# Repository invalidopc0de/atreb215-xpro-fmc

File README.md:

# ATREB215-XPRO FMC Adapter

This repo contains the schematics and PCB layout for a board to adapt
the SATA connectors on the ATREB215 breakout board to the FMC connector 
on a Lattice CrossLink-NX development board

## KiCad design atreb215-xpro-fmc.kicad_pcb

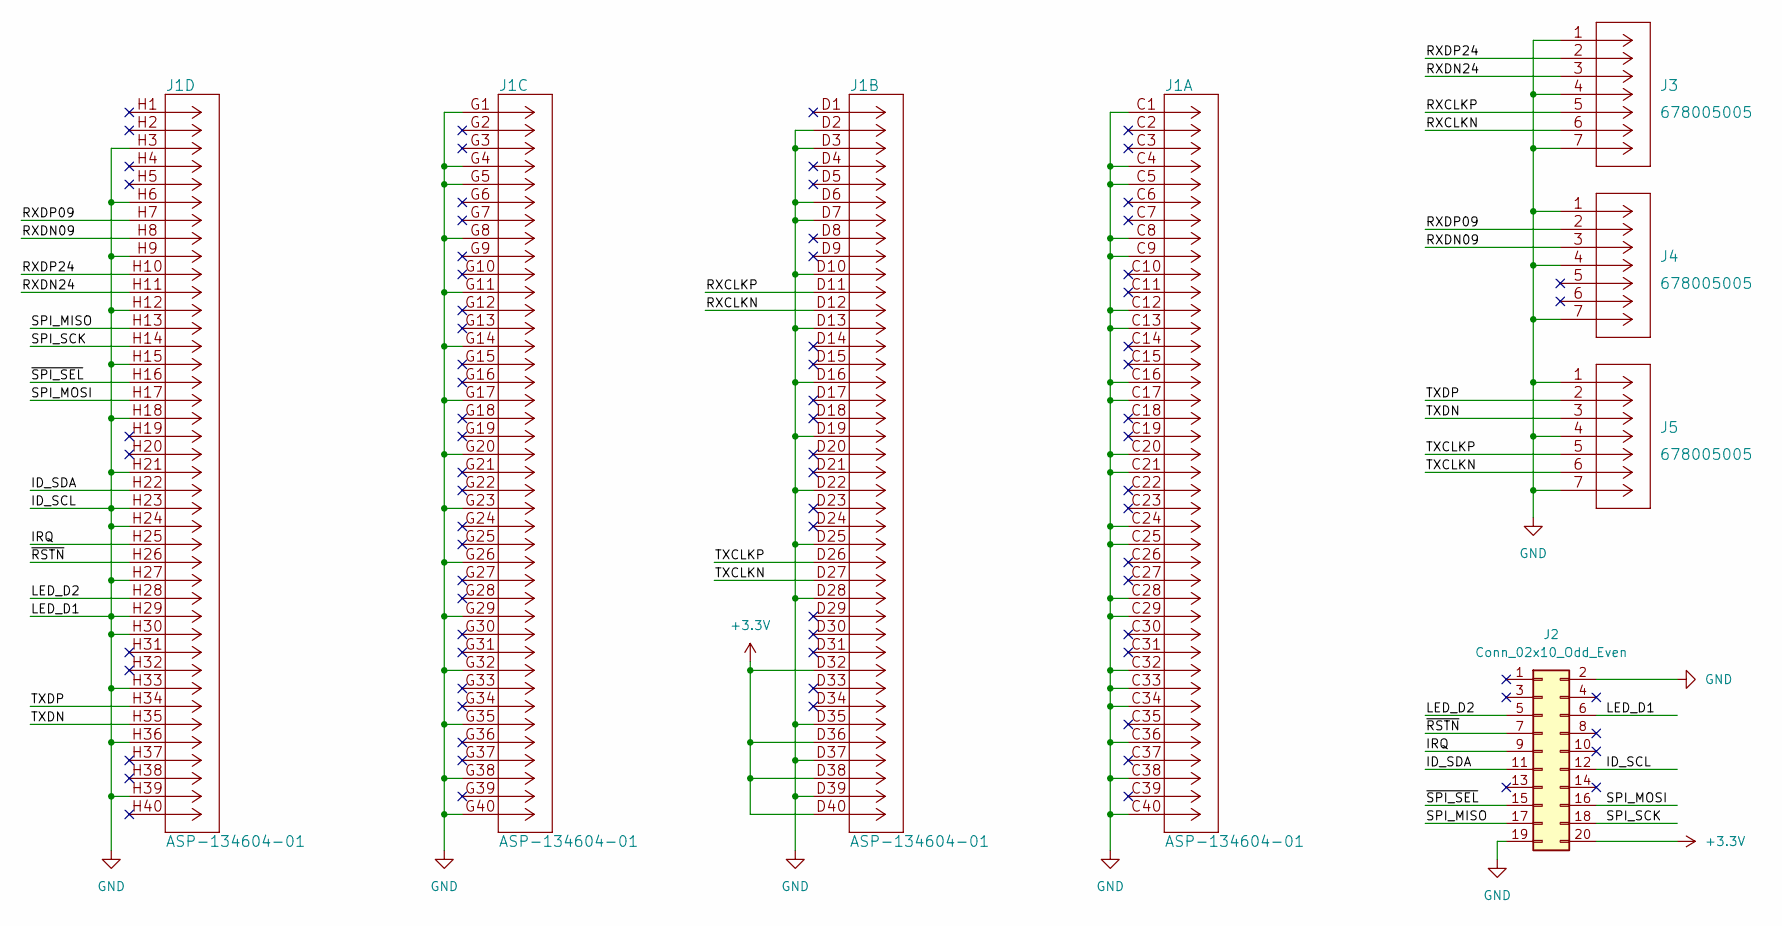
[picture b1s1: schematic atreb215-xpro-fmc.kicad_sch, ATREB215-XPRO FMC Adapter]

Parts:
J1: ASP-134604-01
J2: Conn_02x10_Odd_Even; PinHeader_2x10_P2.54mm_Horizontal
J3, J4, J5: 678005005

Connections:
+3.3V: J1.D32, J1.D36, J1.D38, J1.D40, J2.20
/ID_SDA: J1.H22, J2.11
/IRQ: J1.H25, J2.9
/LED_D2: J1.H28, J2.5
/RXCLKN: J1.D12, J3.6
/RXCLKP: J1.D11, J3.5
/RXDN09: J1.H8, J4.3
/RXDN24: J1.H11, J3.3
/RXDP09: J1.H7, J4.2
/RXDP24: J1.H10, J3.2
/SPI_MISO: J1.H13, J2.17
/SPI_MOSI: J1.H17, J2.16
/SPI_SCK: J1.H14, J2.18
/TXCLKN: J1.D27, J5.6
/TXCLKP: J1.D26, J5.5
/TXDN: J1.H35, J5.3
/TXDP: J1.H34, J5.2
/~RSTN: J1.H26, J2.7
/~SPI_SEL: J1.H16, J2.15
GND: J1.C1, J1.C4, J1.C5, J1.C8, J1.C9, J1.C12, J1.C13, J1.C16, J1.C17, J1.C20, J1.C21, J1.C24, J1.C25, J1.C28, J1.C29, J1.C32, J1.C33, J1.C34, J1.C36, J1.C38, J1.C40, J1.D2, J1.D3, J1.D6, J1.D7, J1.D10, J1.D13, J1.D16, J1.D19, J1.D22, J1.D25, J1.D28, J1.D35, J1.D37, J1.D39, J1.G1, J1.G4, J1.G5, J1.G8, J1.G11, J1.G14, J1.G17, J1.G20, J1.G23, J1.G26, J1.G29, J1.G32, J1.G35, J1.G38, J1.G40, J1.H3, J1.H6, J1.H9, J1.H12, J1.H15, J1.H18, J1.H21, J1.H23, J1.H24, J1.H27, J1.H29, J1.H30, J1.H33, J1.H36, J1.H39, J2.2, J2.6, J2.12, J2.19, J3.1, J3.4, J3.7, J4.1, J4.4, J4.7, J5.1, J5.4, J5.7

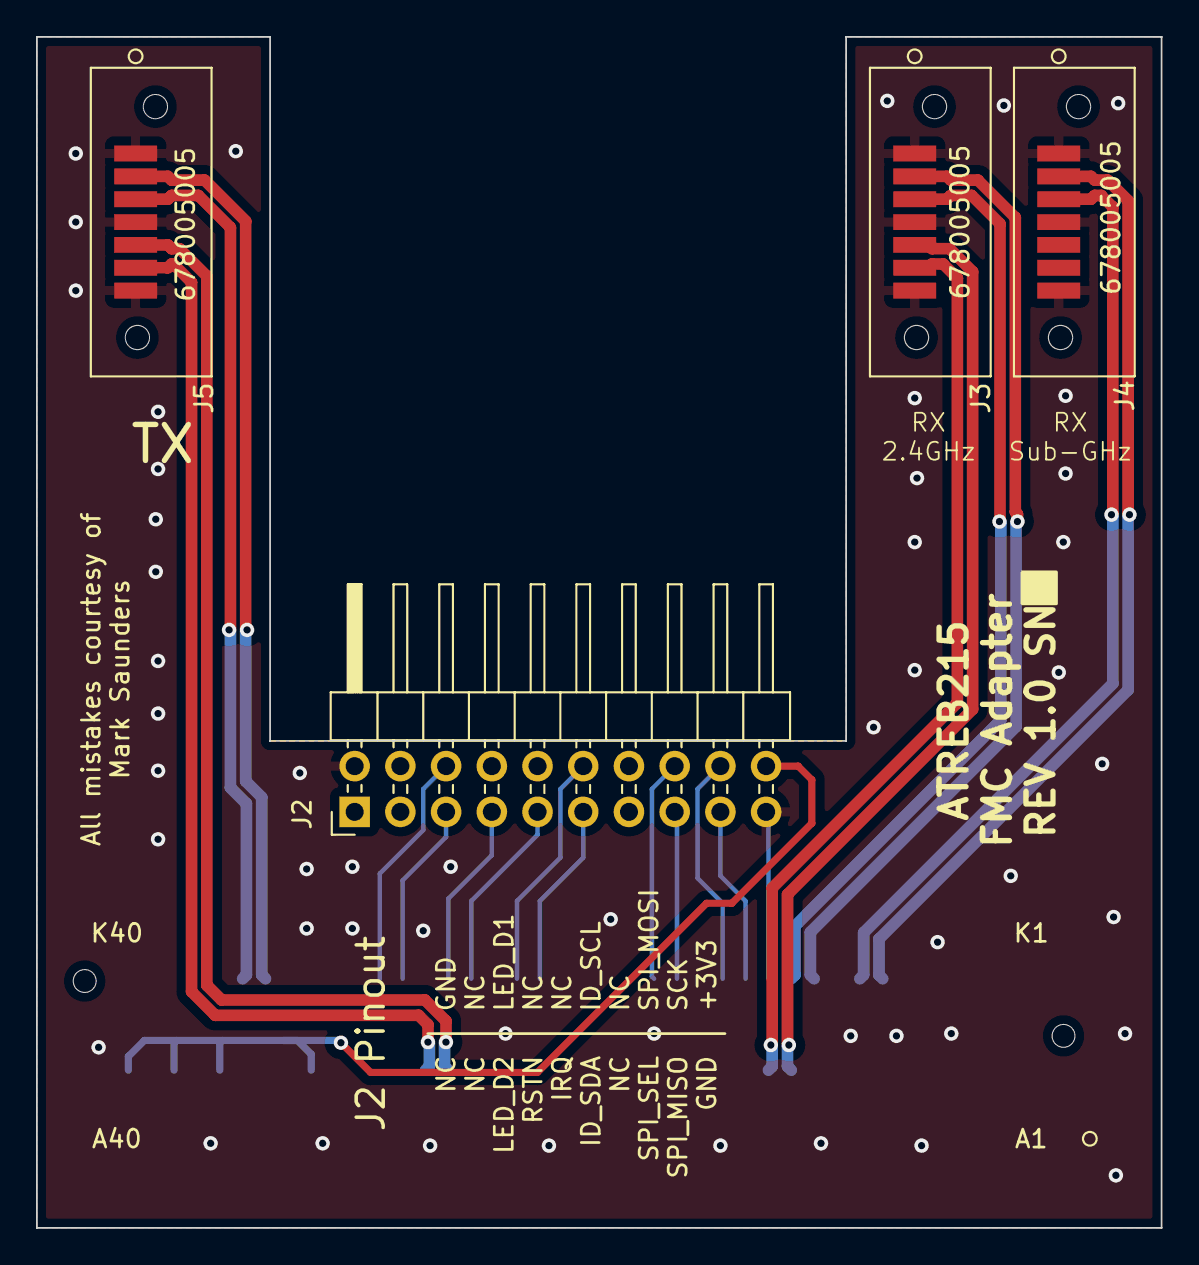
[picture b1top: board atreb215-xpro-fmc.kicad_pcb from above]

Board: 2 copper layers, 62.5 x 66.2 mm, 5 parts (1 on the bottom side), 20 nets.

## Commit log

2022-12-07 Add schematic PDF

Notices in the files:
parts and their libraries:
Copyright 2021 Accelerated Designs. All rights reserved.
